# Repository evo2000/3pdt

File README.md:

# 3pdt
Breakout board for 3pdt footswitches.

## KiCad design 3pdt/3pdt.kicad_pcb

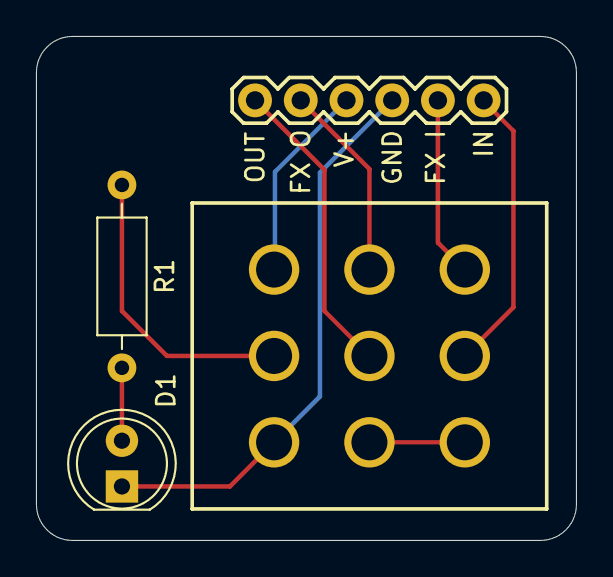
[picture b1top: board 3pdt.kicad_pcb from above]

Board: 2 copper layers, 30.0 x 28.0 mm, 4 parts (0 on the bottom side), 9 nets.

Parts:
D1: LED; LED_D5.0mm
J1: Conn_01x06_Female; 1X06
R1: R; R_Axial_DIN0207_L6.3mm_D2.5mm_P10.16mm_Horizontal
S1: SWITCH-3PDT-PTH-STOMP; STOMP_SWITCH_3PDT

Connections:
9V: J1.3, S1.P$1
GND: D1.1, J1.4, S1.P$3
unnamed: D1.2, R1.2
unnamed: J1.1, S1.P$5
unnamed: J1.2, S1.P$4
unnamed: J1.5, S1.P$7
unnamed: J1.6, S1.P$8
unnamed: R1.1, S1.P$2
unnamed: S1.P$6, S1.P$9

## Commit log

2022-11-04 add hardware files
